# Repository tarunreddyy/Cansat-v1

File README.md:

# CanSat

Project Repo conatining the schematics, Board and Gerber files of all PCBs for The Cansat

Block diagram can be opened using Draw.io desktop app or visit www.draw.io

This Design is patented and cannot be used for commercial purpose.

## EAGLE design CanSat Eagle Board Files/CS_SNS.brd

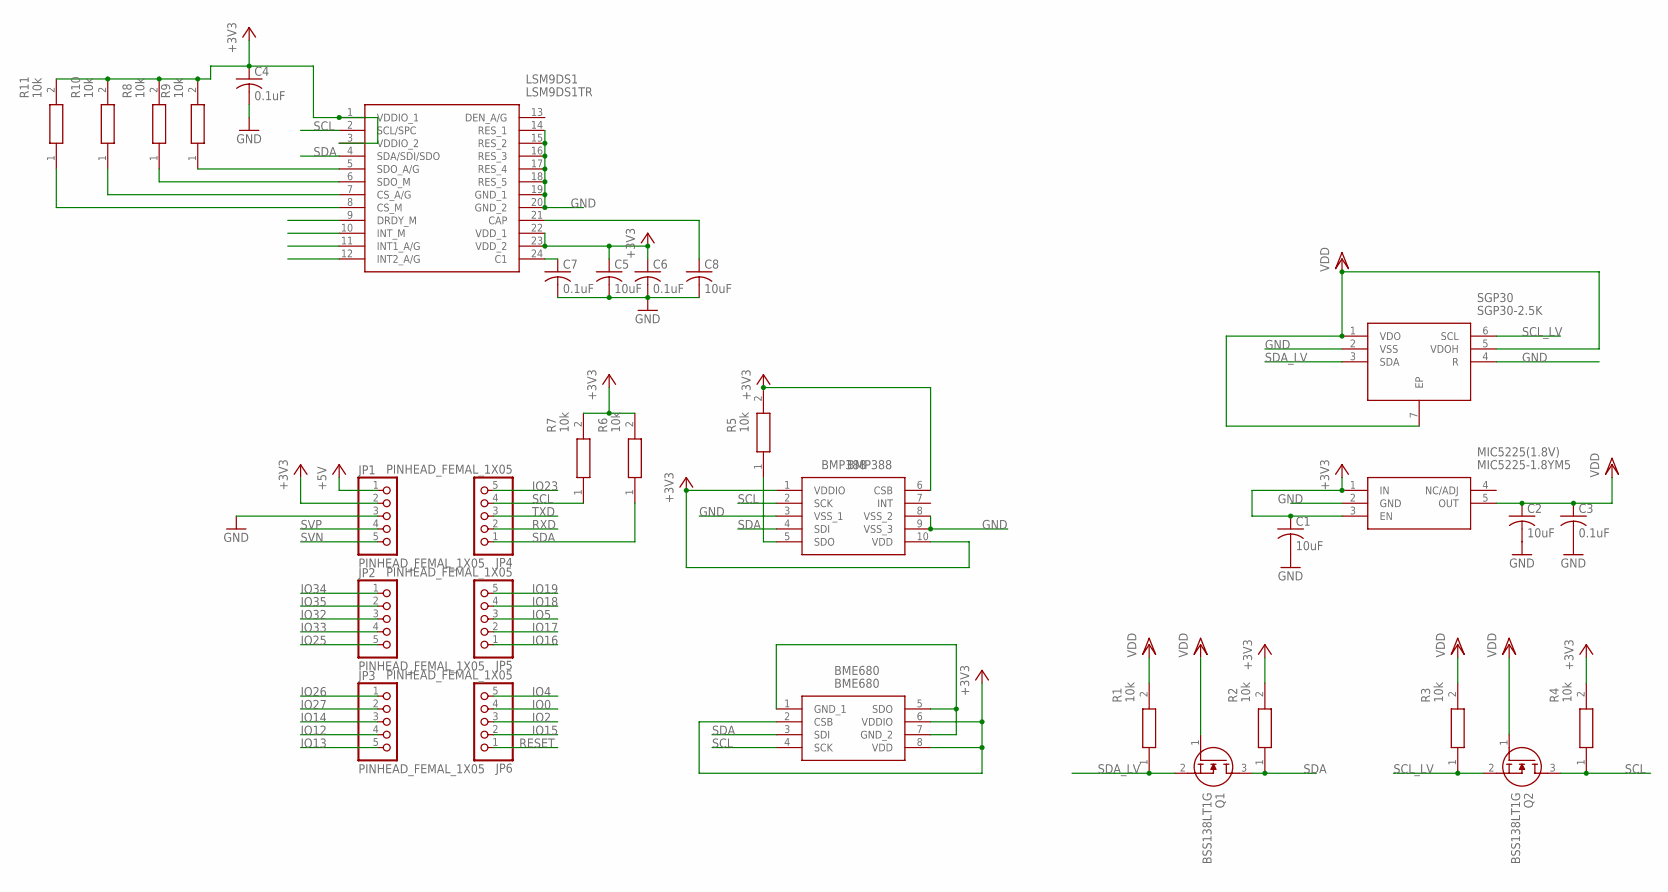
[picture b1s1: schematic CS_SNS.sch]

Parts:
BME680: BME680
BMP388: BMP388
C1, C2, C5, C8: 10uF; C0805
C3, C4, C6, C7: 0.1uF; C0805
JP1, JP2, JP3, JP4, JP5, JP6: PINHEAD_FEMAL_1X05; 1X05F
LSM9DS1: LSM9DS1TR; LGA-24L(3X3.5X1MM)
MIC5225(1.8V): MIC5225-1.8YM5; SOT95P280X145-5N
Q1, Q2: BSS138LT1G; SOT96P237X111-3N
R1, R2, R3, R4, R5, R6, R7, R8, R9, R10, R11: 10k; RESC2012X60N
SGP30: SGP30-2.5K; SON80P245X245X90-7N

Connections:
+3V3: BME680.2 (CSB), BME680.6 (VDDIO), BME680.8 (VDD), BMP388.1 (VDDIO), BMP388.6 (CSB), BMP388.10 (VDD), C1.1, C4.1, C5.1, C6.1, JP1.2, LSM9DS1.1 (VDDIO_1), LSM9DS1.3 (VDDIO_2), LSM9DS1.22 (VDD_1), LSM9DS1.23 (VDD_2), MIC5225(1.8V).1 (IN), MIC5225(1.8V).3 (EN), R2.2, R4.2, R5.2, R6.2, R7.2, R8.2, R9.2, R10.2, R11.2
+5V: JP1.1
GND: BMP388.3 (VSS_1), BMP388.8 (VSS_2), BMP388.9 (VSS_3), C1.2, C2.2, C3.2, C4.2, C5.2, C6.2, C7.2, C8.2, JP1.3, LSM9DS1.14 (RES_1), LSM9DS1.15 (RES_2), LSM9DS1.16 (RES_3), LSM9DS1.17 (RES_4), LSM9DS1.18 (RES_5), LSM9DS1.19 (GND_1), LSM9DS1.20 (GND_2), MIC5225(1.8V).2 (GND), SGP30.2 (VSS), SGP30.4 (R)
IO0: JP6.4
IO2: JP6.3
IO4: JP6.5
IO5: JP5.3
IO12: JP3.4
IO13: JP3.5
IO14: JP3.3
IO15: JP6.2
IO16: JP5.1
IO17: JP5.2
IO18: JP5.4
IO19: JP5.5
IO23: JP4.5
IO25: JP2.5
IO26: JP3.1
IO27: JP3.2
IO32: JP2.3
IO33: JP2.4
IO34: JP2.1
IO35: JP2.2
unnamed: BMP388.5 (SDO), R5.1
unnamed: BME680.1 (GND_1), BME680.5 (SDO), BME680.7 (GND_2)
unnamed: LSM9DS1.5 (SDO_A/G), R9.1
unnamed: LSM9DS1.6 (SDO_M), R8.1
unnamed: C7.1, LSM9DS1.24 (C1)
unnamed: C8.1, LSM9DS1.21 (CAP)
unnamed: LSM9DS1.7 (CS_A/G), R10.1
unnamed: LSM9DS1.8 (CS_M), R11.1
RESET: JP6.1
RXD: JP4.2
SCL: BME680.4 (SCK), BMP388.2 (SCK), JP4.4, LSM9DS1.2 (SCL/SPC), Q2.3 (D), R4.1, R7.1
SCL_LV: Q2.2 (S), R3.1, SGP30.6 (SCL)
SDA: BME680.3 (SDI), BMP388.4 (SDI), JP4.1, LSM9DS1.4 (SDA/SDI/SDO), Q1.3 (D), R2.1, R6.1
SDA_LV: Q1.2 (S), R1.1, SGP30.3 (SDA)
SVN: JP1.5
SVP: JP1.4
TXD: JP4.3
VDD: C2.1, C3.1, MIC5225(1.8V).5 (OUT), Q1.1 (G), Q2.1 (G), R1.2, R3.2, SGP30.1 (VDO), SGP30.5 (VDOH), SGP30.7 (EP)

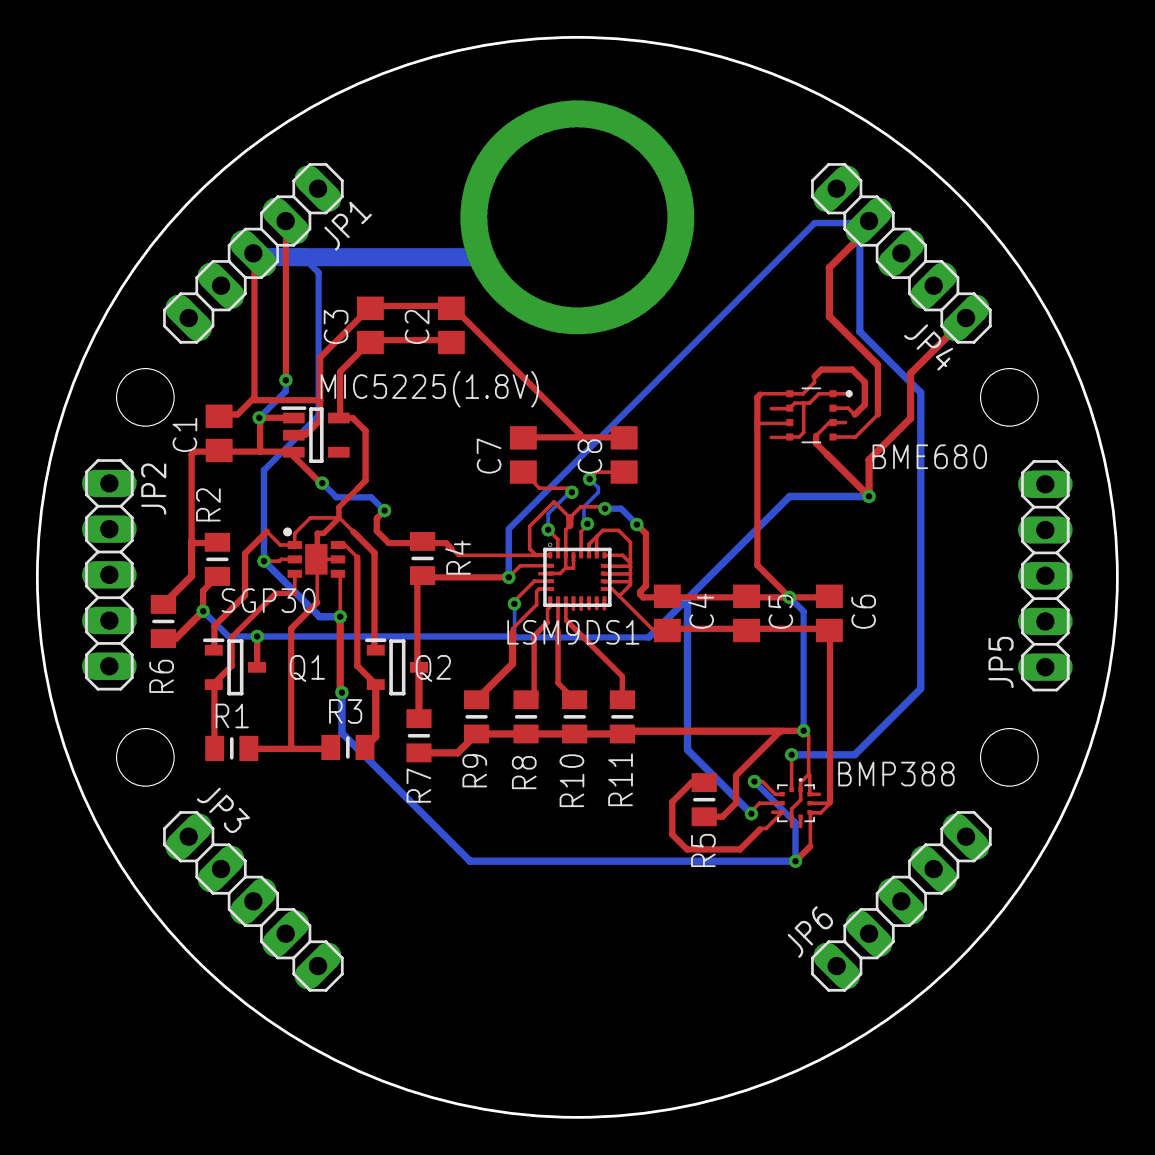
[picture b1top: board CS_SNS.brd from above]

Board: 2 copper layers, 60.0 x 60.0 mm, 32 parts (0 on the bottom side), 15 nets.

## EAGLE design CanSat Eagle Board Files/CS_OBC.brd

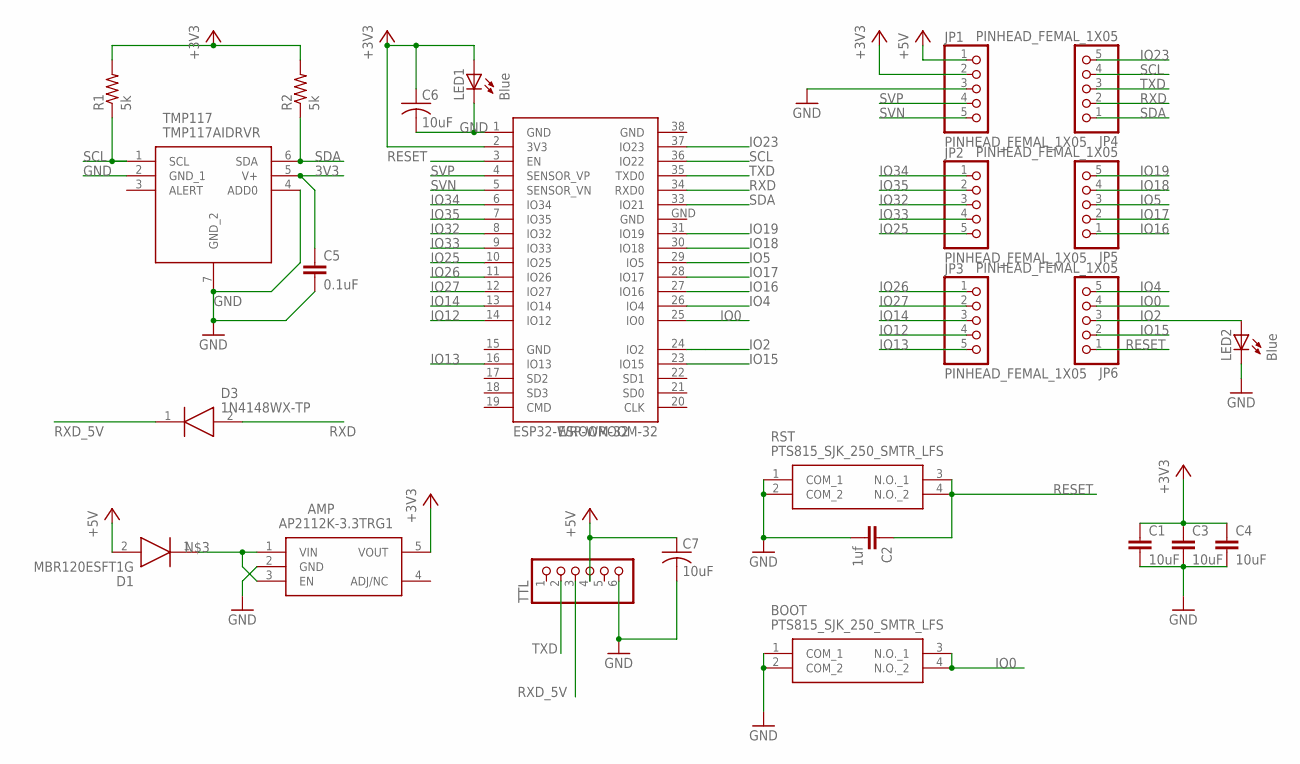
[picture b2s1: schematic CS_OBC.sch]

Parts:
AMP: AP2112K-3.3TRG1; SOT95P282X130-5N
BOOT: PTS815_SJK_250_SMTR_LFS; PTS815SJK250SMTRLFS
C1, C3, C4: 10uF; C0805
C2: 1uf; C0805
C5: 0.1uF; C0805
C6, C7: 10uF; C1206
D1: MBR120ESFT1G; SODFL3616X98N
D3: 1N4148WX-TP; SOD2512X115N
ESP32-WROOM-32: ESP-WROOM-32
JP1, JP2, JP3, JP4, JP5, JP6: PINHEAD_FEMAL_1X05; 1X05F
LED1, LED2: Blue; CHIPLED_0805
R1, R2: 5k; R0805
RST: PTS815_SJK_250_SMTR_LFS; PTS815SJK250SMTRLFS
TMP117: TMP117AIDRVR; SON65P200X200X80-7N
TTL: PINHD-1X6/90; 1X06/90

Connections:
3V3: C5.1, TMP117.5 (V+)
+3V3: AMP.5 (VOUT), C1.1, C3.1, C4.1, C6.1, ESP32-WROOM-32.2 (3V3), JP1.2, LED1.A, R1.2, R2.2
+5V: C7.1, D1.2 (A), JP1.1, TTL.4
GND: AMP.2 (GND), BOOT.1 (COM_1), BOOT.2 (COM_2), C1.2, C2.2, C3.2, C4.2, C5.2, C6.2, C7.2, ESP32-WROOM-32.1 (GND), ESP32-WROOM-32.15 (GND), ESP32-WROOM-32.38 (GND), ESP32-WROOM-32.GND, JP1.3, LED1.C, LED2.C, RST.1 (COM_1), RST.2 (COM_2), TMP117.2 (GND_1), TMP117.4 (ADD0), TMP117.7 (GND_2), TTL.6
IO0: BOOT.3 (N.O._1), BOOT.4 (N.O._2), ESP32-WROOM-32.25 (IO0), JP6.4
IO2: ESP32-WROOM-32.24 (IO2), JP6.3, LED2.A
IO4: ESP32-WROOM-32.26 (IO4), JP6.5
IO5: ESP32-WROOM-32.29 (IO5), JP5.3
IO12: ESP32-WROOM-32.14 (IO12), JP3.4
IO13: ESP32-WROOM-32.16 (IO13), JP3.5
IO14: ESP32-WROOM-32.13 (IO14), JP3.3
IO15: ESP32-WROOM-32.23 (IO15), JP6.2
IO16: ESP32-WROOM-32.27 (IO16), JP5.1
IO17: ESP32-WROOM-32.28 (IO17), JP5.2
IO18: ESP32-WROOM-32.30 (IO18), JP5.4
IO19: ESP32-WROOM-32.31 (IO19), JP5.5
IO23: ESP32-WROOM-32.37 (IO23), JP4.5
IO25: ESP32-WROOM-32.10 (IO25), JP2.5
IO26: ESP32-WROOM-32.11 (IO26), JP3.1
IO27: ESP32-WROOM-32.12 (IO27), JP3.2
IO32: ESP32-WROOM-32.8 (IO32), JP2.3
IO33: ESP32-WROOM-32.9 (IO33), JP2.4
IO34: ESP32-WROOM-32.6 (IO34), JP2.1
IO35: ESP32-WROOM-32.7 (IO35), JP2.2
unnamed: AMP.1 (VIN), AMP.3 (EN), D1.1 (K)
RESET: C2.1, ESP32-WROOM-32.3 (EN), JP6.1, RST.3 (N.O._1), RST.4 (N.O._2)
RXD: D3.2 (A), ESP32-WROOM-32.34 (RXD0), JP4.2
RXD_5V: D3.1 (K), TTL.3
SCL: ESP32-WROOM-32.36 (IO22), JP4.4, R1.1, TMP117.1 (SCL)
SDA: ESP32-WROOM-32.33 (IO21), JP4.1, R2.1, TMP117.6 (SDA)
SVN: ESP32-WROOM-32.5 (SENSOR_VN), JP1.5
SVP: ESP32-WROOM-32.4 (SENSOR_VP), JP1.4
TXD: ESP32-WROOM-32.35 (TXD0), JP4.3, TTL.2

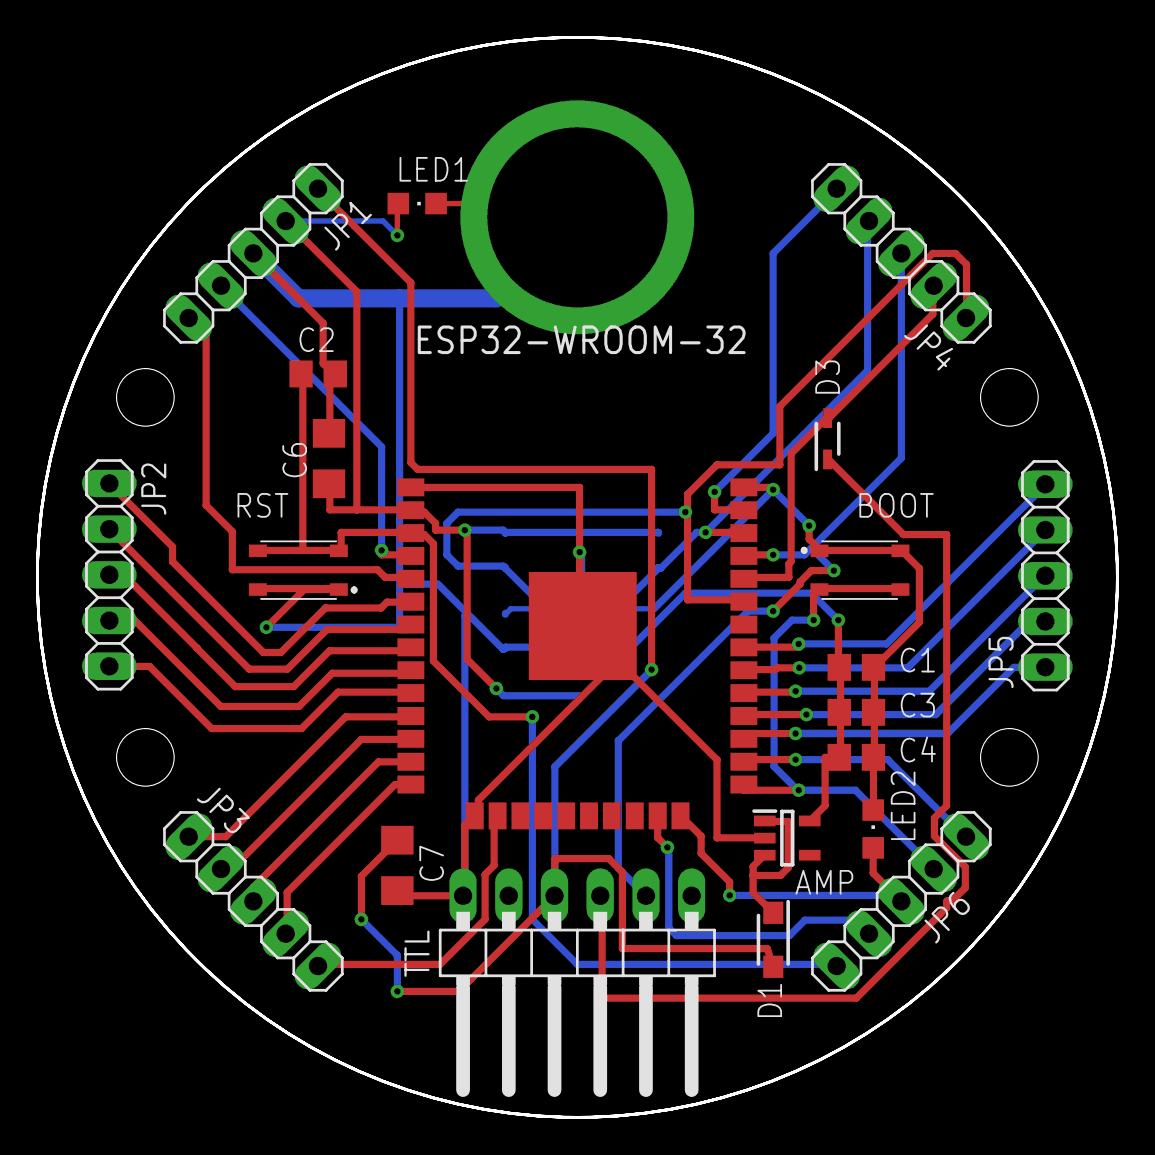
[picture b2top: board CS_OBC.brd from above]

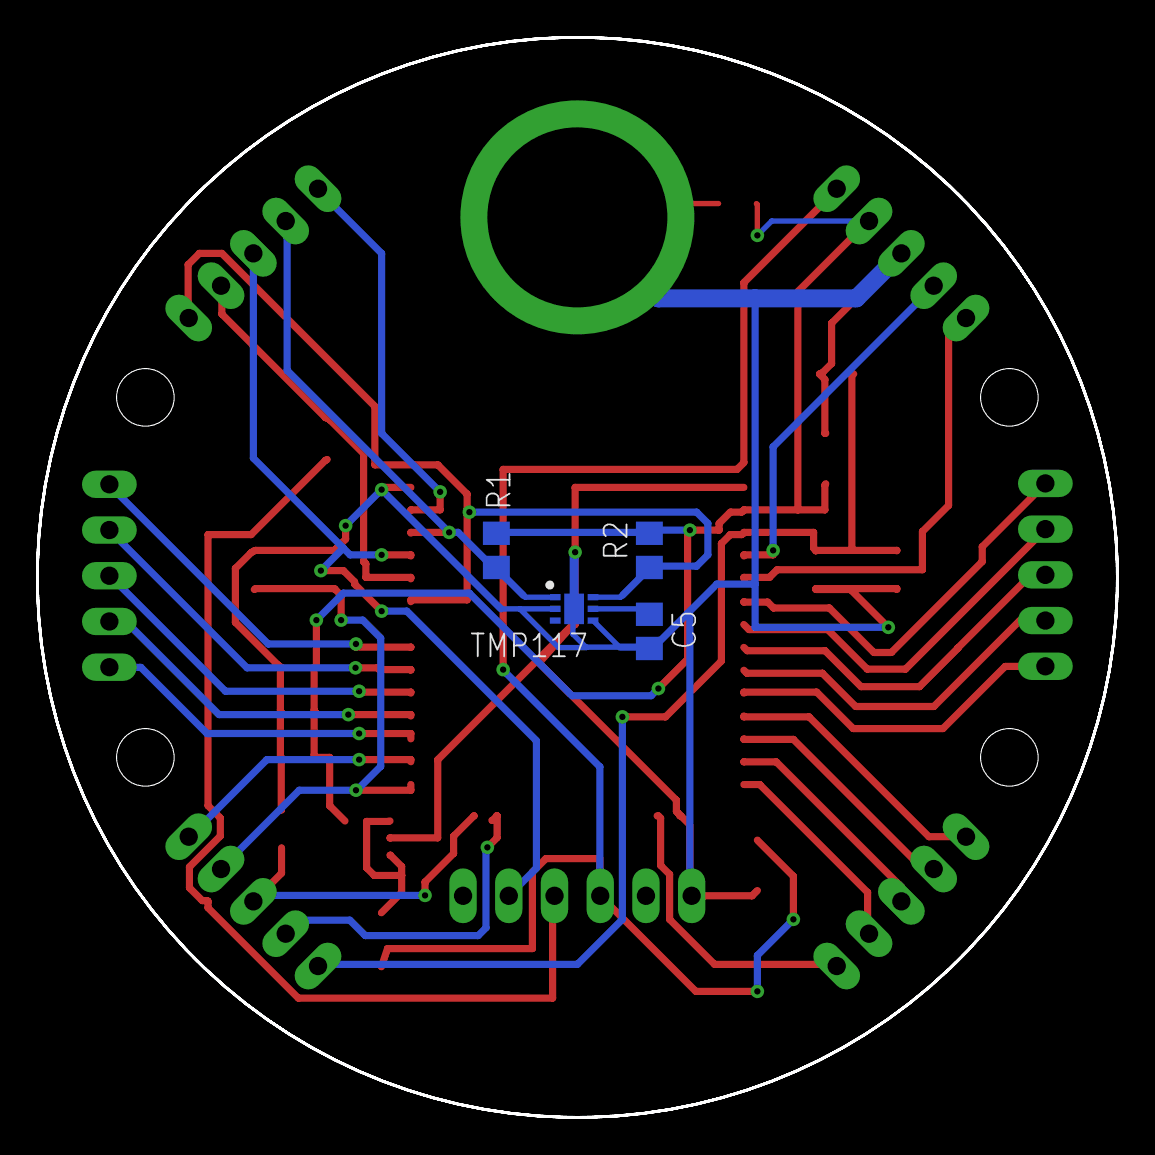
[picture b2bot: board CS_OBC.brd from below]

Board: 2 copper layers, 60.0 x 60.0 mm, 25 parts (4 on the bottom side), 33 nets.

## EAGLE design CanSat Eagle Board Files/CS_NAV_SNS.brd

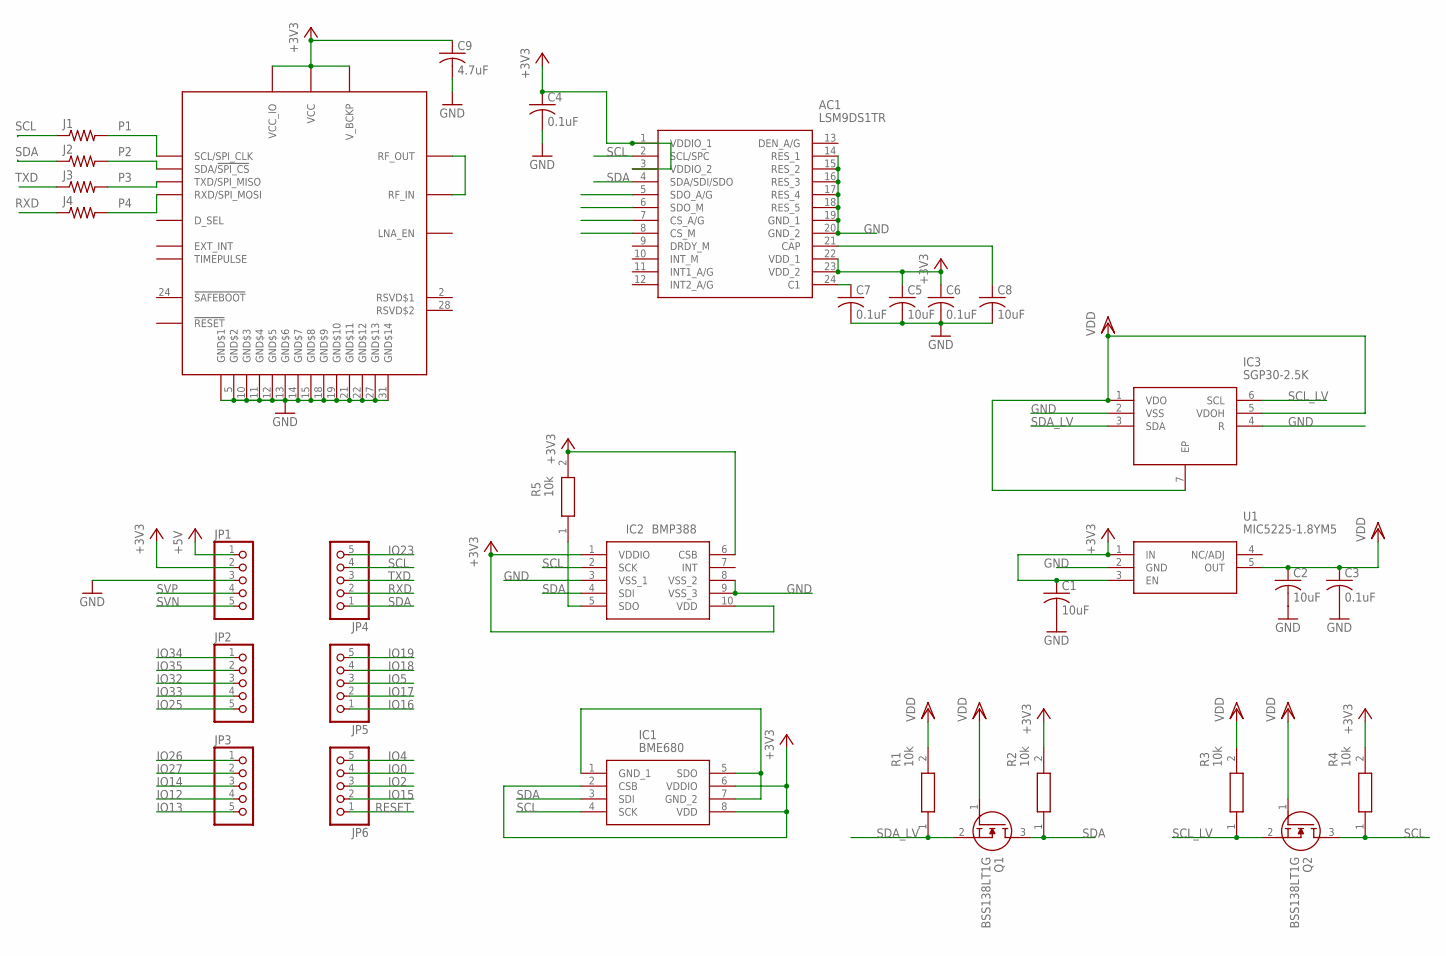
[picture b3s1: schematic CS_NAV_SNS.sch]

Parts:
AC1: LSM9DS1TR; LGA-24L(3X3.5X1MM)
C1, C2, C5, C8: 10uF; C0805
C3, C4, C6, C7: 0.1uF; C0805
C9: 4.7uF; C0805
IC1: BME680
IC2: BMP388
IC3: SGP30-2.5K; SON80P245X245X90-7N
J1, J2, J3, J4: R-US_R1206; R1206
JP1, JP2, JP3, JP4, JP5, JP6: PINHD-1X5; 1X05
Q1, Q2: BSS138LT1G; SOT96P237X111-3N
R1, R2, R3, R4, R5: 10k; RESC2012X60N
U1: MIC5225-1.8YM5; SOT95P280X145-5N
U$1: CAM-M8

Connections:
+3V3: AC1.1 (VDDIO_1), AC1.3 (VDDIO_2), AC1.22 (VDD_1), AC1.23 (VDD_2), C1.1, C4.1, C5.1, C6.1, C9.1, IC1.2 (CSB), IC1.6 (VDDIO), IC1.8 (VDD), IC2.1 (VDDIO), IC2.6 (CSB), IC2.10 (VDD), JP1.2, R2.2, R4.2, R5.2, U1.1 (IN), U1.3 (EN), U$1.1 (VCC_IO), U$1.8 (V_BCKP), U$1.9 (VCC)
+5V: JP1.1
GND: AC1.14 (RES_1), AC1.15 (RES_2), AC1.16 (RES_3), AC1.17 (RES_4), AC1.18 (RES_5), AC1.19 (GND_1), AC1.20 (GND_2), C1.2, C2.2, C3.2, C4.2, C5.2, C6.2, C7.2, C8.2, C9.2, IC2.3 (VSS_1), IC2.8 (VSS_2), IC2.9 (VSS_3), IC3.2 (VSS), IC3.4 (R), JP1.3, U1.2 (GND), U$1.4 (GND$1), U$1.5 (GND$2), U$1.10 (GND$3), U$1.11 (GND$4), U$1.12 (GND$5), U$1.13 (GND$6), U$1.14 (GND$7), U$1.15 (GND$8), U$1.18 (GND$9), U$1.19 (GND$10), U$1.21 (GND$11), U$1.22 (GND$12), U$1.27 (GND$13), U$1.31 (GND$14)
IO0: JP6.4
IO2: JP6.3
IO4: JP6.5
IO5: JP5.3
IO12: JP3.4
IO13: JP3.5
IO14: JP3.3
IO15: JP6.2
IO16: JP5.1
IO17: JP5.2
IO18: JP5.4
IO19: JP5.5
IO23: JP4.5
IO25: JP2.5
IO26: JP3.1
IO27: JP3.2
IO32: JP2.3
IO33: JP2.4
IO34: JP2.1
IO35: JP2.2
unnamed: U$1.16 (RF_OUT), U$1.17 (RF_IN)
unnamed: IC2.5 (SDO), R5.1
unnamed: IC1.1 (GND_1), IC1.5 (SDO), IC1.7 (GND_2)
unnamed: AC1.24 (C1), C7.1
unnamed: AC1.21 (CAP), C8.1
P1: J1.2, U$1.6 (SCL/SPI_CLK)
P2: J2.2, U$1.3 (SDA/!SPI_CS)
P3: J3.2, U$1.25 (TXD/SPI_MISO)
P4: J4.2, U$1.26 (RXD/SPI_MOSI)
RESET: JP6.1
RXD: J4.1, JP4.2
SCL: AC1.2 (SCL/SPC), IC1.4 (SCK), IC2.2 (SCK), J1.1, JP4.4, Q2.3 (D), R4.1
SCL_LV: IC3.6 (SCL), Q2.2 (S), R3.1
SDA: AC1.4 (SDA/SDI/SDO), IC1.3 (SDI), IC2.4 (SDI), J2.1, JP4.1, Q1.3 (D), R2.1
SDA_LV: IC3.3 (SDA), Q1.2 (S), R1.1
SVN: JP1.5
SVP: JP1.4
TXD: J3.1, JP4.3
VDD: C2.1, C3.1, IC3.1 (VDO), IC3.5 (VDOH), IC3.7 (EP), Q1.1 (G), Q2.1 (G), R1.2, R3.2, U1.5 (OUT)

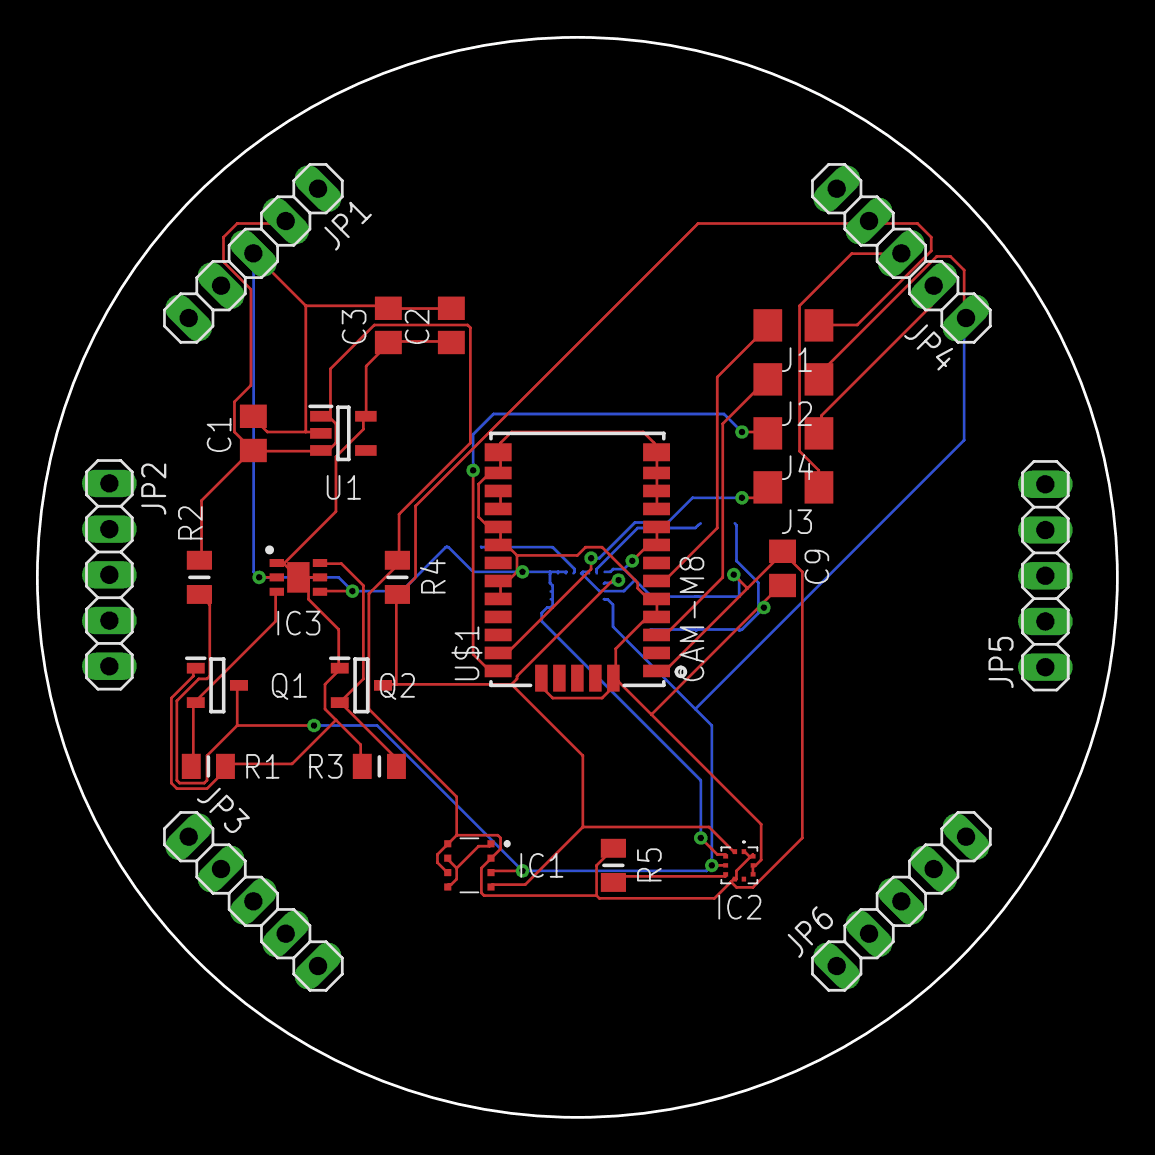
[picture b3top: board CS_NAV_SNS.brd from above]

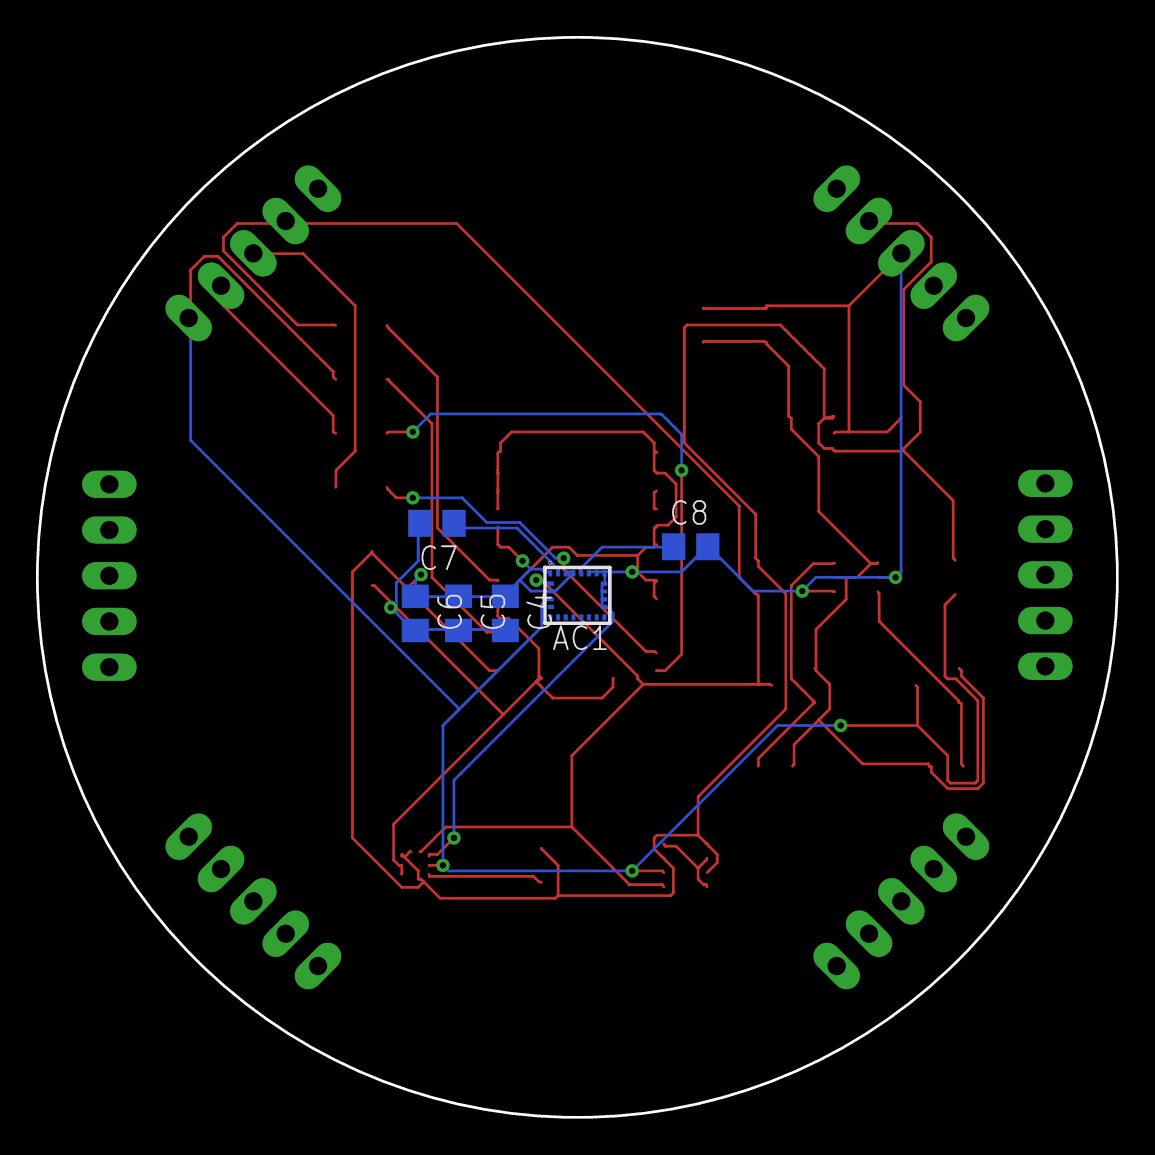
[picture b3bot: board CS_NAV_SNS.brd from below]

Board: 2 copper layers, 60.0 x 60.0 mm, 32 parts (6 on the bottom side), 18 nets.

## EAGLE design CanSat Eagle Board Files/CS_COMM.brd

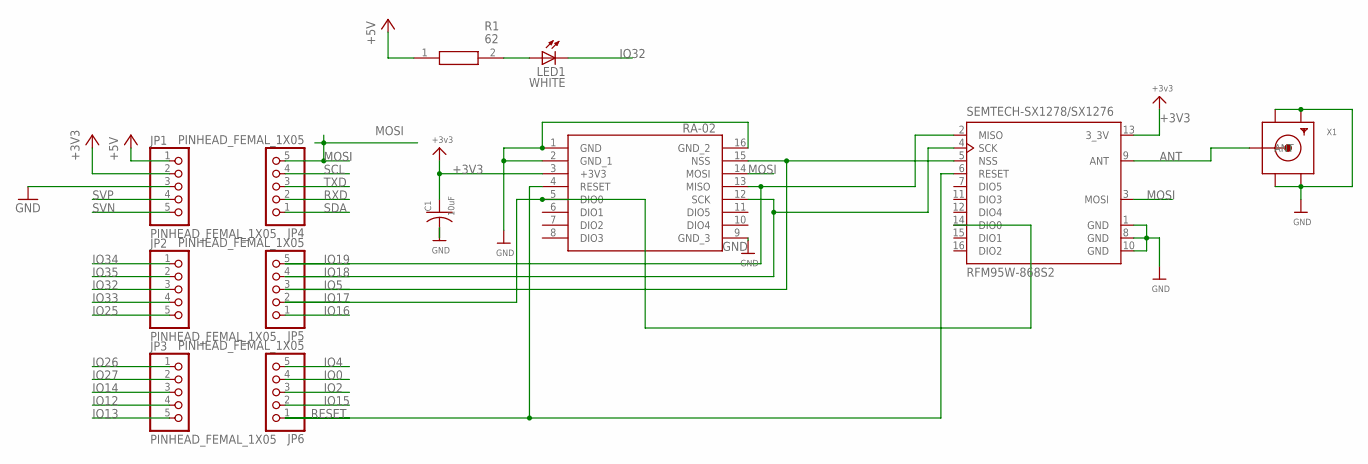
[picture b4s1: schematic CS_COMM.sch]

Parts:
AI-THINKER_RA-02: RA-02SMD-16; SON200P1600X1650X200-16
C1: 10uF; C0805
JP1, JP2, JP3, JP4, JP5, JP6: PINHEAD_FEMAL_1X05; 1X05F
LED1: WHITE; CHIPLED_1206
R1: 62; RESC2012X60N
SEMTECH-SX1278/SX1276: RFM95W-868S2; XCVR_RFM95W-868S2
X1: SMACONNECTOR; SMA90_DIP

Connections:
+3V3: AI-THINKER_RA-02.3 (+3V3), C1.1, JP1.2, SEMTECH-SX1278/SX1276.13 (3_3V)
+5V: JP1.1, R1.1
ANT: SEMTECH-SX1278/SX1276.9 (ANT), X1.ANTENNA (ANT)
GND: AI-THINKER_RA-02.1 (GND), AI-THINKER_RA-02.2 (GND_1), AI-THINKER_RA-02.9 (GND_3), AI-THINKER_RA-02.16 (GND_2), C1.2, JP1.3, SEMTECH-SX1278/SX1276.1 (GND), SEMTECH-SX1278/SX1276.8 (GND), SEMTECH-SX1278/SX1276.10 (GND), X1.GND1, X1.GND2, X1.GND3, X1.GND4
IO0: JP6.4
IO2: JP6.3
IO4: JP6.5
IO5: AI-THINKER_RA-02.15 (NSS), JP5.3, SEMTECH-SX1278/SX1276.5 (NSS)
IO12: JP3.4
IO13: JP3.5
IO14: JP3.3
IO15: JP6.2
IO16: JP5.1
IO17: AI-THINKER_RA-02.5 (DIO0), JP5.2, SEMTECH-SX1278/SX1276.14 (DIO0)
IO18: AI-THINKER_RA-02.12 (SCK), JP5.4, SEMTECH-SX1278/SX1276.4 (SCK)
IO19: AI-THINKER_RA-02.13 (MISO), JP5.5, SEMTECH-SX1278/SX1276.2 (MISO)
IO25: JP2.5
IO26: JP3.1
IO27: JP3.2
IO32: JP2.3, LED1.C
IO33: JP2.4
IO34: JP2.1
IO35: JP2.2
MOSI: AI-THINKER_RA-02.14 (MOSI), JP4.5, SEMTECH-SX1278/SX1276.3 (MOSI)
unnamed: LED1.A, R1.2
RESET: AI-THINKER_RA-02.4 (RESET), JP6.1, SEMTECH-SX1278/SX1276.6 (RESET)
RXD: JP4.2
SCL: JP4.4
SDA: JP4.1
SVN: JP1.5
SVP: JP1.4
TXD: JP4.3

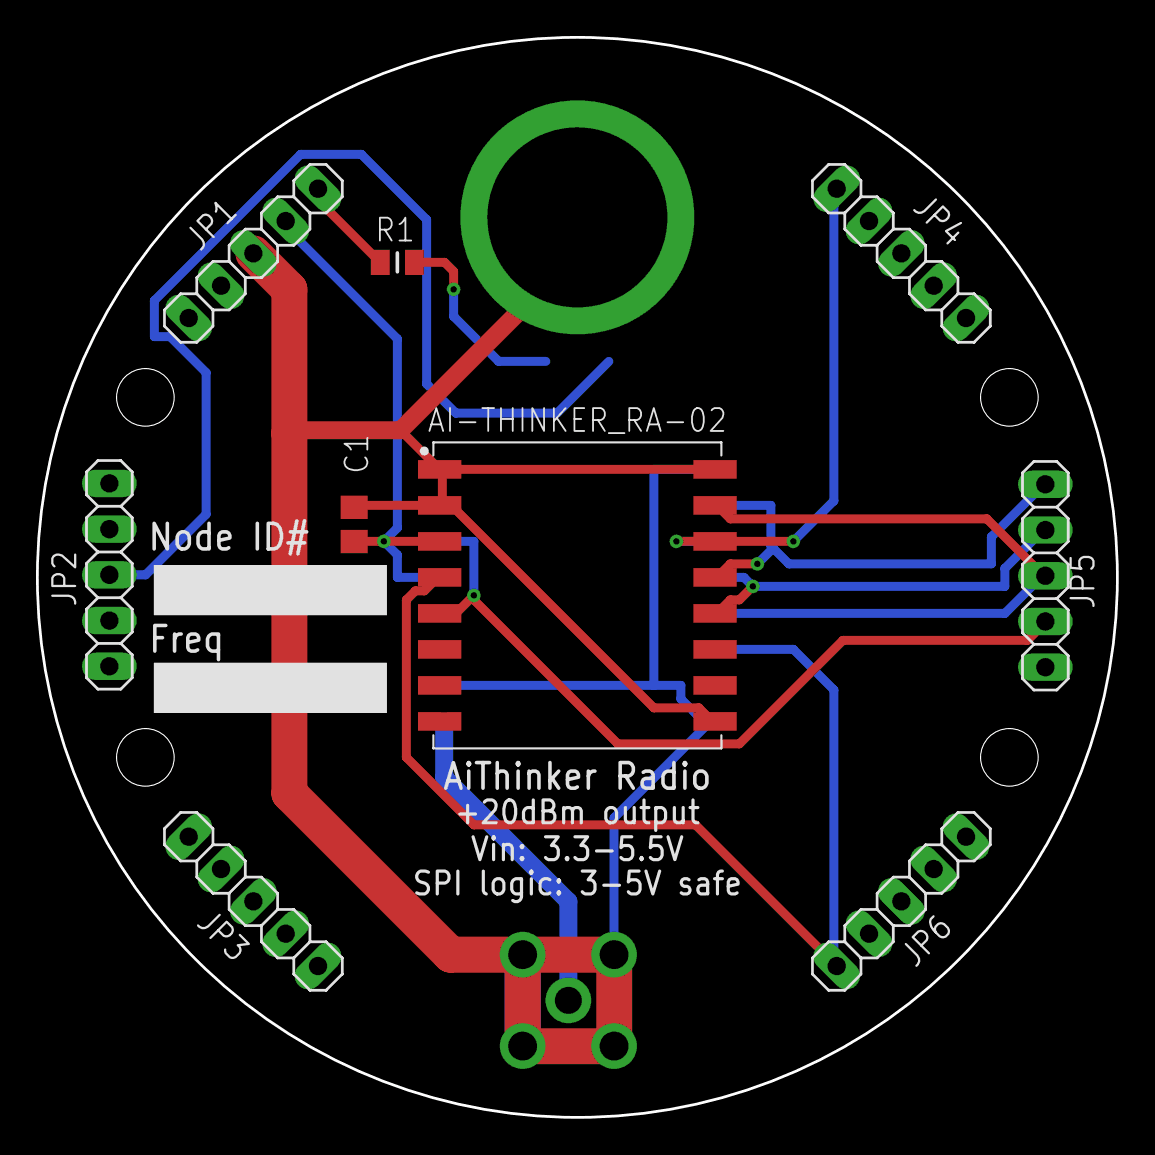
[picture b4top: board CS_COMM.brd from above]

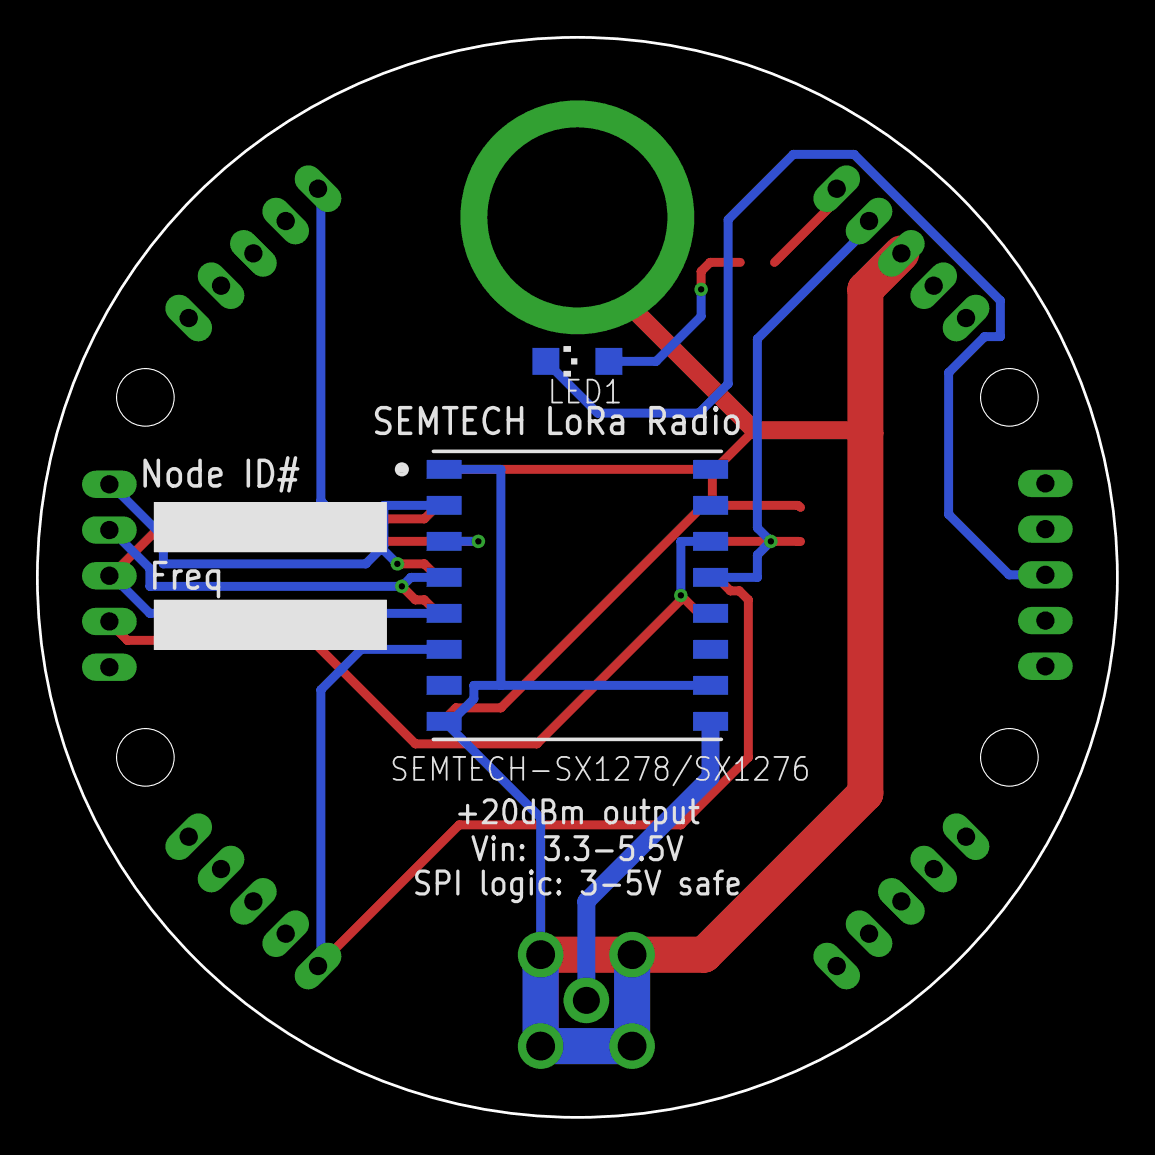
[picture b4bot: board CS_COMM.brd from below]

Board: 2 copper layers, 60.0 x 60.0 mm, 12 parts (2 on the bottom side), 12 nets.

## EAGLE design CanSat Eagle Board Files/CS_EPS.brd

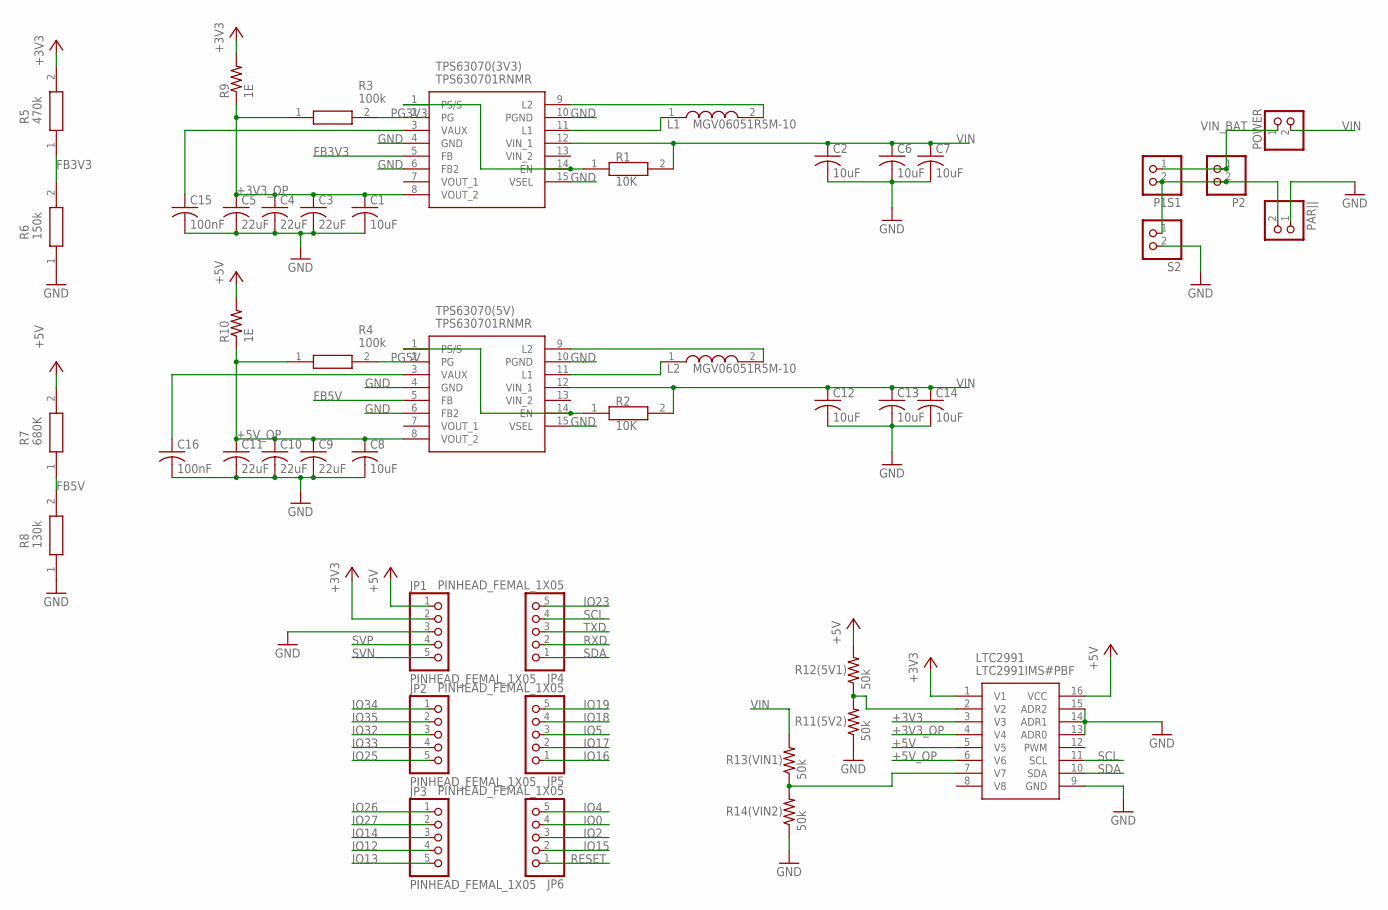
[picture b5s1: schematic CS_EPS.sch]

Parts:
C1, C2, C8, C12: 10uF; C0603K
C3, C4, C5, C9, C10, C11: 22uF; C0805K
C6, C7, C13, C14: 10uF; C0805K
C15, C16: 100nF; C0402
JP1, JP2, JP3, JP4, JP5, JP6: PINHEAD_FEMAL_1X05; 1X05F
L1, L2: MGV06051R5M-10; INDPM7367X530N
LTC2991: LTC2991IMS#PBF; SOP50P490X110-16N
P1S1, P2: JST_2PIN-THM; JST-PH-2-THM
PAR||: PINHD-1X2; 1X02
POWER: PINHD-1X2; 1X02
R1, R2: 10K; RESC2012X60N
R3, R4: 100k; RESC2012X60N
R5: 470k; RESC2012X60N
R6: 150k; RESC2012X60N
R7: 680K; RESC2012X60N
R8: 130k; RESC2012X60N
R9, R10: 1E; R0805
R11(5V2), R12(5V1), R13(VIN1), R14(VIN2): 50k; R0805
S2: JST_2PIN-THM; JST-PH-2-THM
TPS63070(3V3), TPS63070(5V): TPS630701RNMR

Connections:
+3V3: JP1.2, LTC2991.1 (V1), LTC2991.3 (V3), R5.2, R9.2
+3V3_OP: C1.1, C3.1, C4.1, C5.1, LTC2991.4 (V4), R3.1, R9.1, TPS63070(3V3).8 (VOUT_2)
+5V: JP1.1, LTC2991.5 (V5), LTC2991.16 (VCC), R7.2, R10.2, R12(5V1).2
+5V_OP: C8.1, C9.1, C10.1, C11.1, LTC2991.6 (V6), R4.1, R10.1, TPS63070(5V).8 (VOUT_2)
FB3V3: R5.1, R6.2, TPS63070(3V3).5 (FB)
FB5V: R7.1, R8.2, TPS63070(5V).5 (FB)
GND: C1.2, C2.2, C3.2, C4.2, C5.2, C6.2, C7.2, C8.2, C9.2, C10.2, C11.2, C12.2, C13.2, C14.2, C15.2, C16.2, JP1.3, LTC2991.9 (GND), LTC2991.13 (ADR0), LTC2991.14 (ADR1), LTC2991.15 (ADR2), PAR||.1, R6.1, R8.1, R11(5V2).1, R14(VIN2).1, S2.2 (1), TPS63070(3V3).4 (GND), TPS63070(3V3).6 (FB2), TPS63070(3V3).10 (PGND), TPS63070(3V3).15 (VSEL), TPS63070(5V).4 (GND), TPS63070(5V).6 (FB2), TPS63070(5V).10 (PGND), TPS63070(5V).15 (VSEL)
IO0: JP6.4
IO2: JP6.3
IO4: JP6.5
IO5: JP5.3
IO12: JP3.4
IO13: JP3.5
IO14: JP3.3
IO15: JP6.2
IO16: JP5.1
IO17: JP5.2
IO18: JP5.4
IO19: JP5.5
IO23: JP4.5
IO25: JP2.5
IO26: JP3.1
IO27: JP3.2
IO32: JP2.3
IO33: JP2.4
IO34: JP2.1
IO35: JP2.2
L11: L1.1, TPS63070(3V3).11 (L1)
L12: L1.2, TPS63070(3V3).9 (L2)
L21: L2.1, TPS63070(5V).11 (L1)
L22: L2.2, TPS63070(5V).9 (L2)
unnamed: P1S1.2 (1), P2.2 (1), PAR||.2, S2.1 (2)
unnamed: LTC2991.2 (V2), R11(5V2).2, R12(5V1).1
unnamed: R1.1, TPS63070(3V3).1 (PS/S), TPS63070(3V3).14 (EN)
unnamed: LTC2991.7 (V7), R13(VIN1).1, R14(VIN2).2
unnamed: R2.1, TPS63070(5V).1 (PS/S), TPS63070(5V).14 (EN)
unnamed: C15.1, TPS63070(3V3).3 (VAUX)
unnamed: C16.1, TPS63070(5V).3 (VAUX)
PG3V3: R3.2, TPS63070(3V3).2 (PG)
PG5V: R4.2, TPS63070(5V).2 (PG)
RESET: JP6.1
RXD: JP4.2
SCL: JP4.4, LTC2991.11 (SCL)
SDA: JP4.1, LTC2991.10 (SDA)
SVN: JP1.5
SVP: JP1.4
TXD: JP4.3
VIN: C2.1, C6.1, C7.1, C12.1, C13.1, C14.1, POWER.2, R1.2, R2.2, R13(VIN1).2, TPS63070(3V3).12 (VIN_1), TPS63070(5V).12 (VIN_1)
VIN_BAT: P1S1.1 (2), P2.1 (2), POWER.1

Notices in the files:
parts and their libraries:
microbuilder: This work is placed in the public domain, and may be freely used for commercial and non-commercial work with the following conditions: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
esp32: Creative Commons Attribution-ShareAlike 4.0 International
